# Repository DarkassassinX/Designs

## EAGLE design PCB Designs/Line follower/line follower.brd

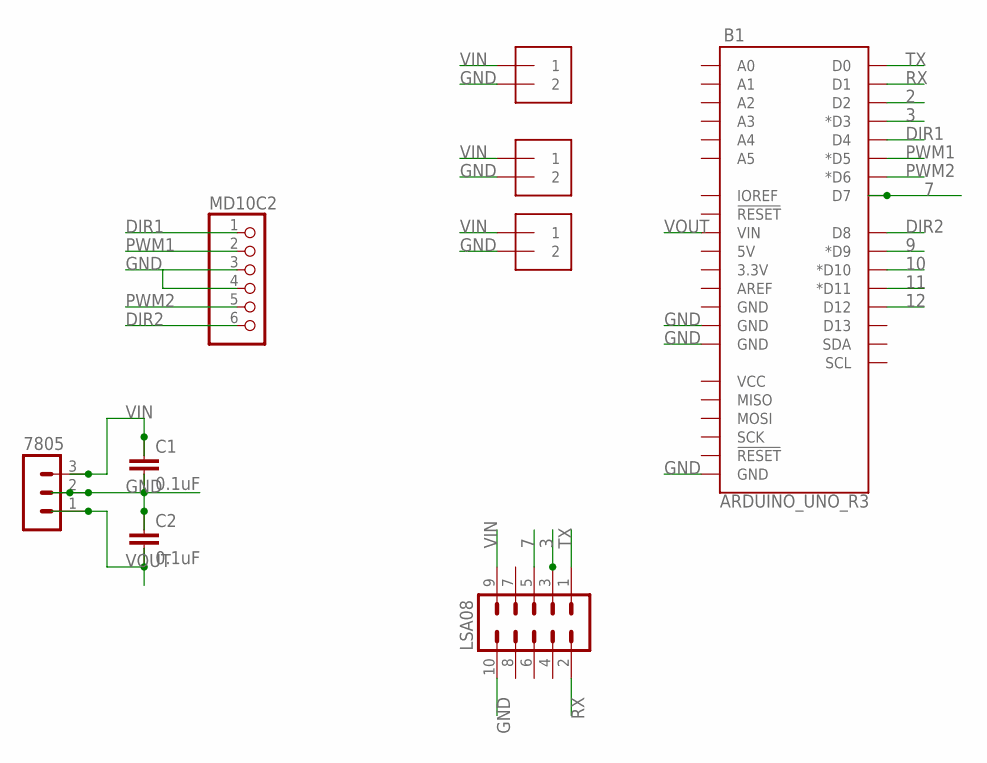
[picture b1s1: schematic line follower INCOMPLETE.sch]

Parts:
7805: MA03-1
B1: ARDUINO_UNO_R3; ARDUINO_R3
C1, C2: 0.1uF; CAP-PTH-SMALL-KIT
LSA08: MA05-2
MD1POWER, MD2POWER: 1X2-3.5MM
MD10C2: PINHD-1X6; 1X06
POWERARDUINO: 1X2-3.5MM

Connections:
2: B1.D2
3: B1.D3 (*D3), LSA08.3
7: B1.D7, LSA08.5
9: B1.D9 (*D9)
10: B1.D10 (*D10)
11: B1.D11 (*D11)
12: B1.D12
DIR1: B1.D4, MD10C2.1
DIR2: B1.D8, MD10C2.6
GND: 7805.2, B1.GND@1 (GND), B1.GND@2 (GND), B1.GND@3 (GND), C1.2, C2.1, LSA08.10, MD1POWER.2, MD2POWER.2, MD10C2.3, MD10C2.4, POWERARDUINO.2
PWM1: B1.D5 (*D5), MD10C2.2
PWM2: B1.D6 (*D6), MD10C2.5
RX: B1.D1, LSA08.2
TX: B1.D0, LSA08.1
VIN: 7805.3, C1.1, LSA08.9, MD1POWER.1, MD2POWER.1, POWERARDUINO.1
VOUT: 7805.1, B1.VIN, C2.2

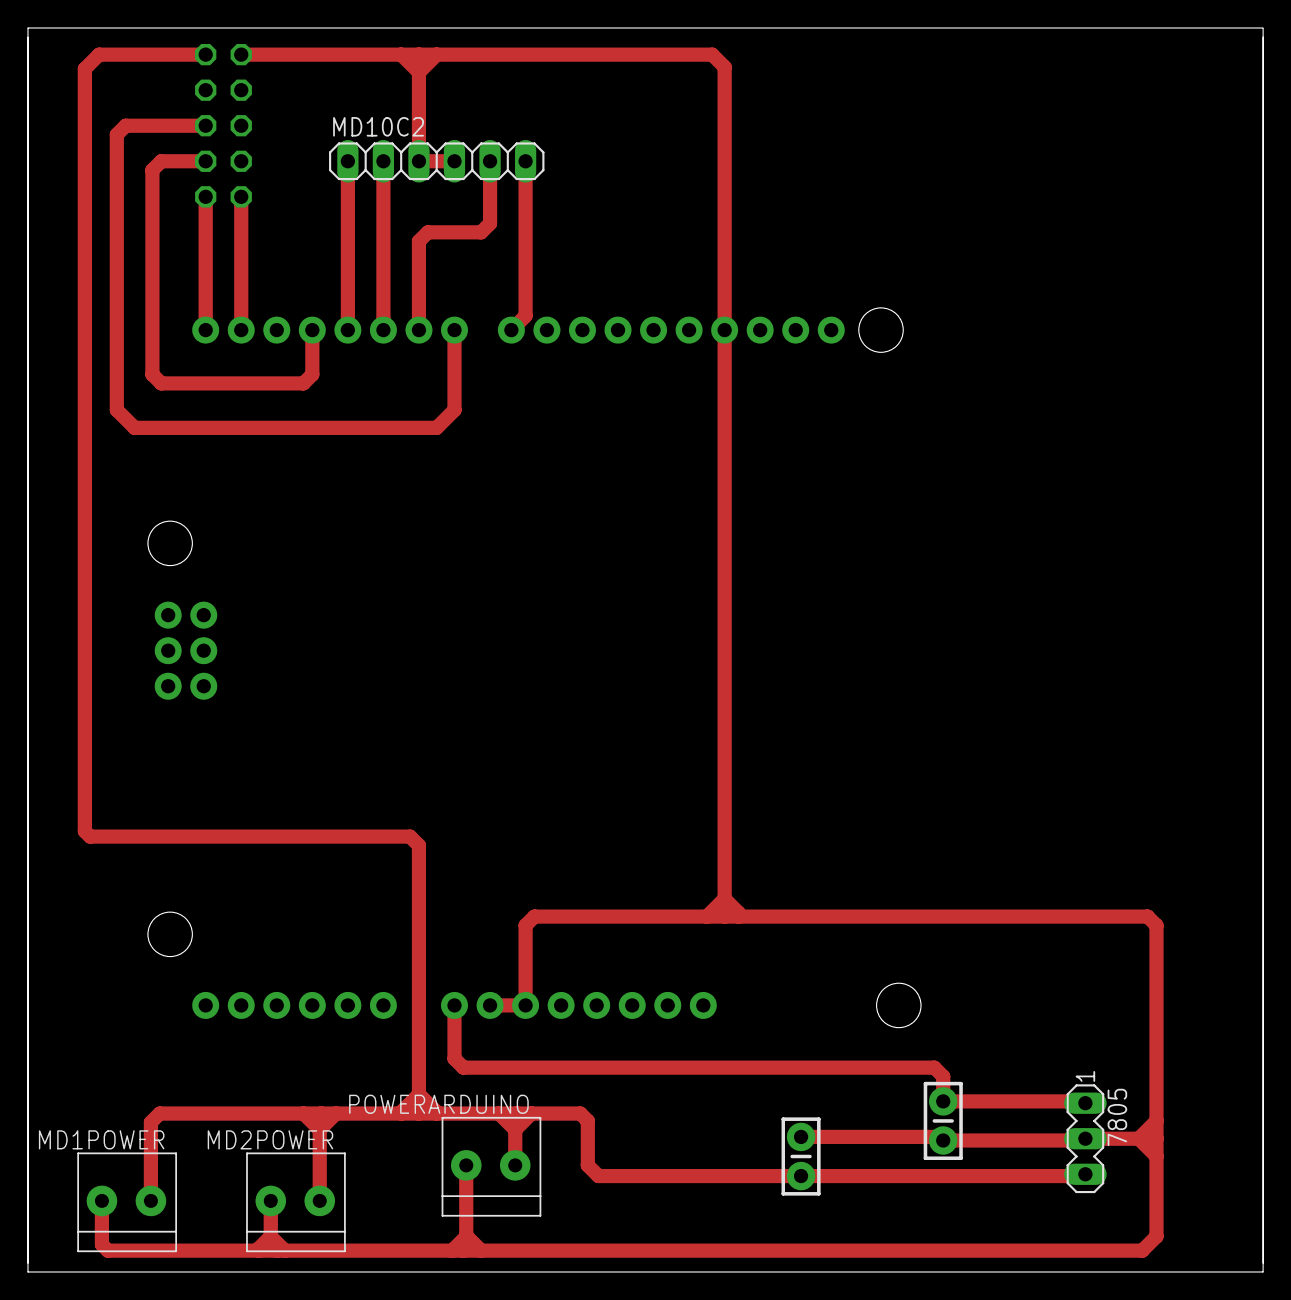
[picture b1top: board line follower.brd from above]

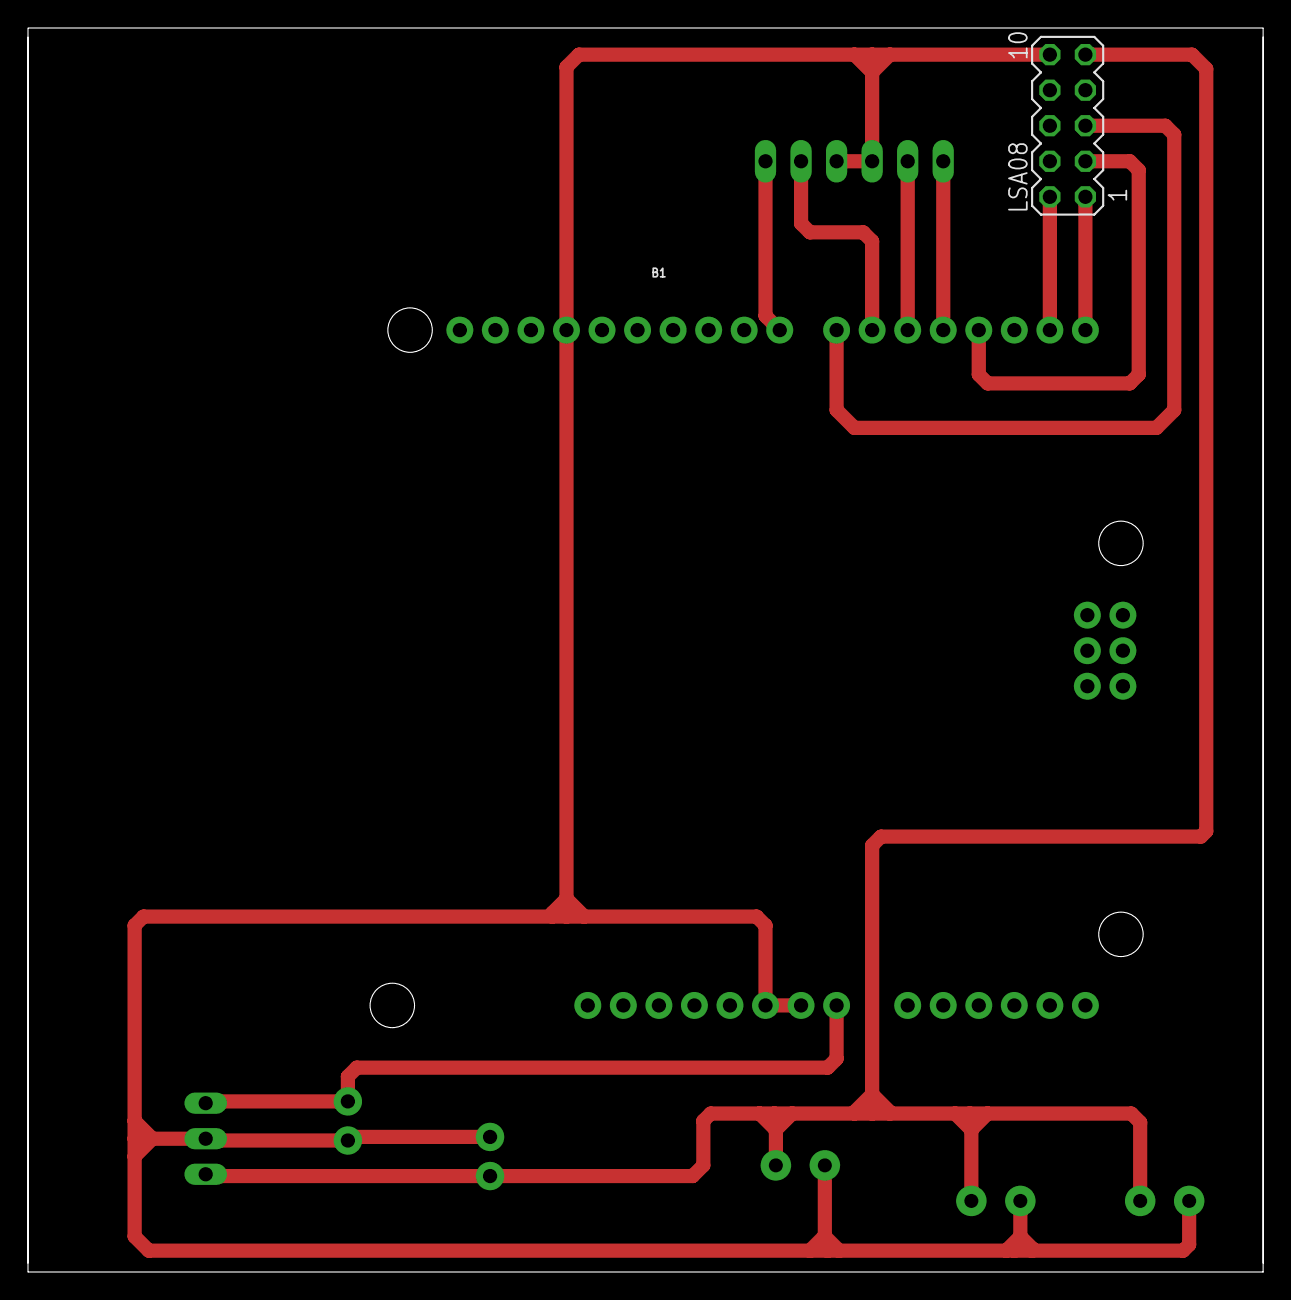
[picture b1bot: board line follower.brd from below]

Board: 2 copper layers, 88.3 x 88.9 mm, 9 parts (2 on the bottom side), 11 nets.

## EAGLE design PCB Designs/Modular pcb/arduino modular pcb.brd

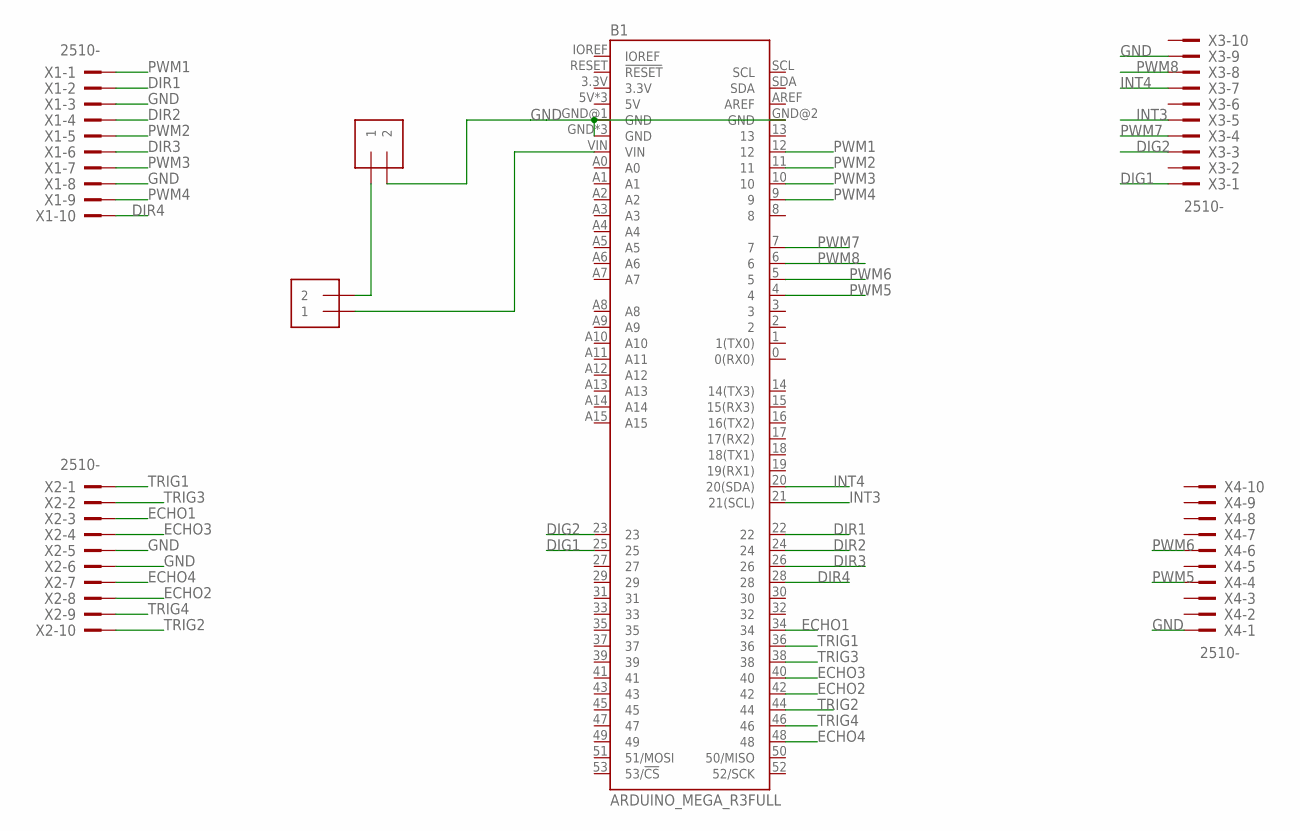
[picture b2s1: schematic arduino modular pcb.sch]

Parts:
B1: ARDUINO_MEGA_R3FULL; ARDUINO_MEGA_NO_SILK
J1, J2: 1X2-3.5MM
X1, X2, X3, X4: 2510-; PAK100/2500-10

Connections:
DIG1: B1.25, X3.1
DIG2: B1.23, X3.3
DIR1: B1.22, X1.2
DIR2: B1.24, X1.4
DIR3: B1.26, X1.6
DIR4: B1.28, X1.10
ECHO1: B1.34, X2.3
ECHO2: B1.42, X2.8
ECHO3: B1.40, X2.4
ECHO4: B1.48, X2.7
GND: B1.GND, B1.GND@1 (GND), B1.GND@2 (GND), B1.GND@3 (GND), B1.GND@4 (GND), J2.2, X1.3, X1.8, X2.5, X2.6, X3.9, X4.1
INT3: B1.21 (21(SCL)), X3.5
INT4: B1.20 (20(SDA)), X3.7
unnamed: J1.2, J2.1
unnamed: B1.VIN, J1.1
PWM1: B1.12, X1.1
PWM2: B1.11, X1.5
PWM3: B1.10, X1.7
PWM4: B1.9, X1.9
PWM5: B1.4, X4.4
PWM6: B1.5, X4.6
PWM7: B1.7, X3.4
PWM8: B1.6, X3.8
TRIG1: B1.36, X2.1
TRIG2: B1.44, X2.10
TRIG3: B1.38, X2.2
TRIG4: B1.46, X2.9

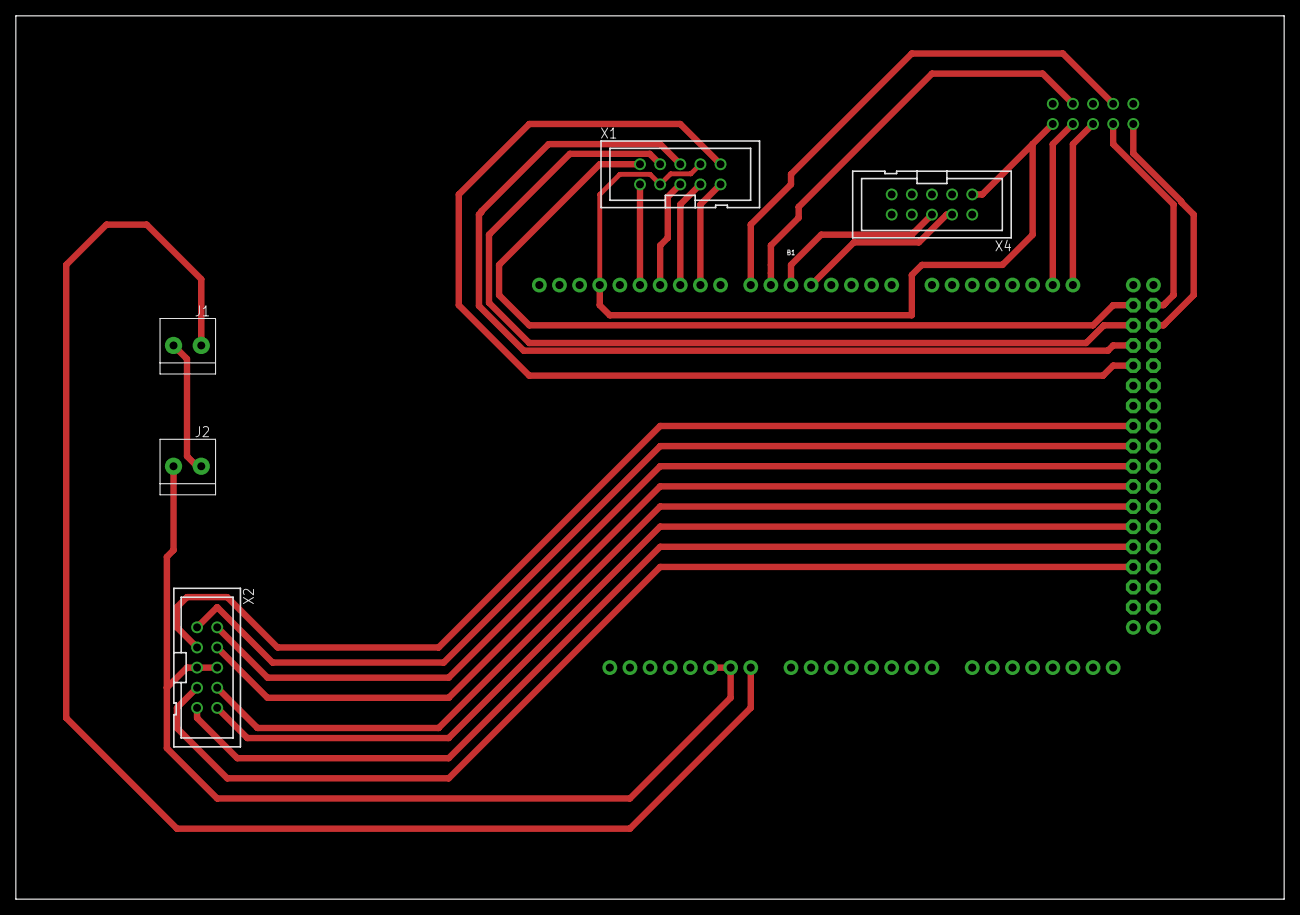
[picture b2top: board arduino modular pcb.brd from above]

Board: 2 copper layers, 160.0 x 111.4 mm, 7 parts (1 on the bottom side), 27 nets.

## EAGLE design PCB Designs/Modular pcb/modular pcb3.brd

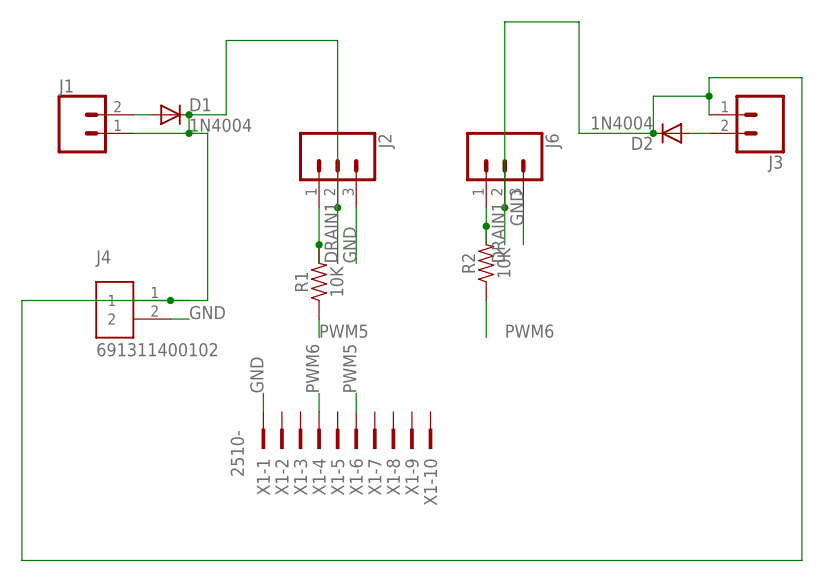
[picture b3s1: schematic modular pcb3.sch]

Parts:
D1, D2: 1N4004; DO41-10
J1, J3: CONN_02; 1X02
J2, J6: 455-1750-1-ND; 1X03
J4: 691311400102; TERMINALBLOCK_PLUGGABLE-2-7.62MM
R1, R2: 10K; 0402-TIGHT
X1: 2510-; PAK100/2500-10

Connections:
DRAIN1: D1.C, D2.C, J1.1, J2.2, J3.1, J4.1, J6.2
GND: J2.3, J4.2, J6.3, X1.1
unnamed: D1.A, J1.2
unnamed: J2.1, R1.2
unnamed: D2.A, J3.2
unnamed: J6.1, R2.2
PWM5: R1.1, X1.6
PWM6: R2.1, X1.4

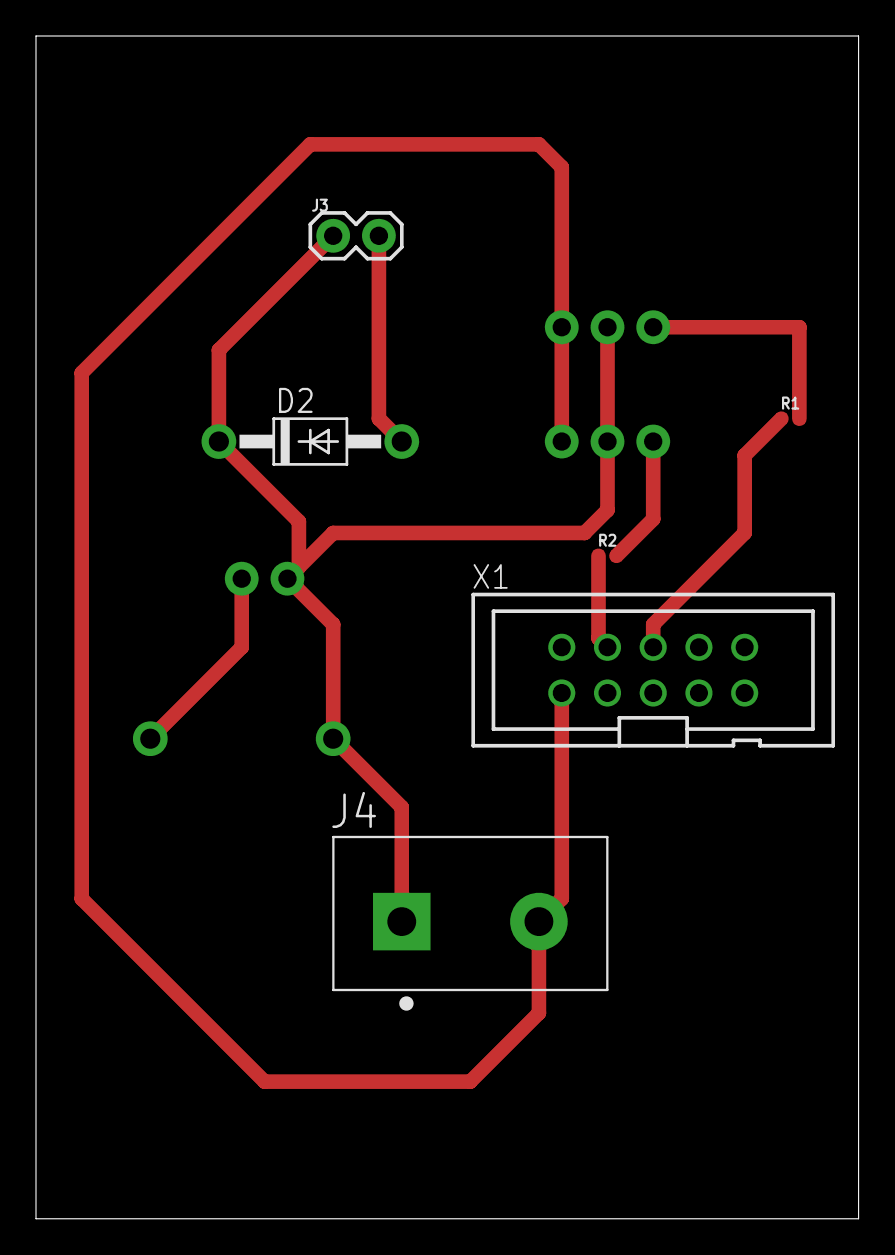
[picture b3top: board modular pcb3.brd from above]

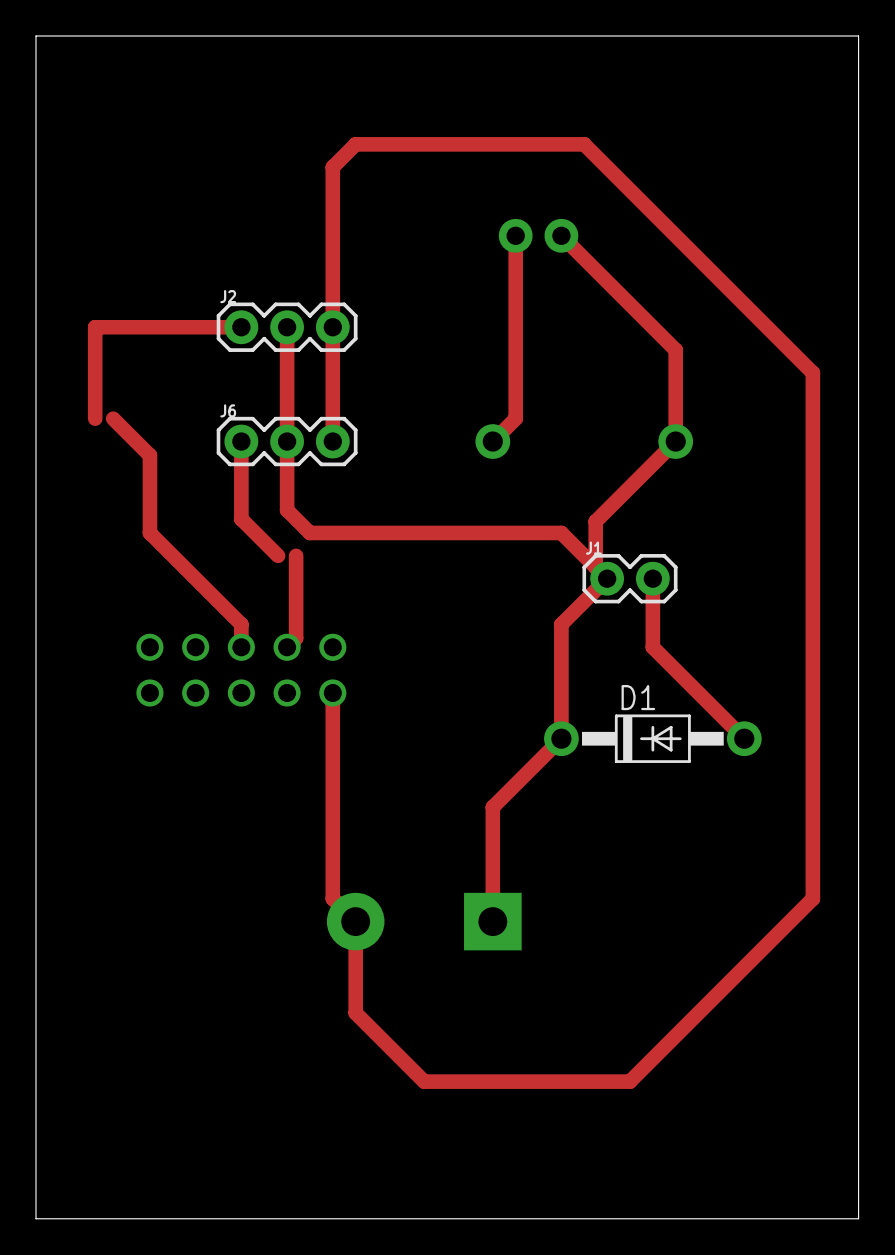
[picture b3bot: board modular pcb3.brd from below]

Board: 2 copper layers, 45.7 x 65.7 mm, 10 parts (4 on the bottom side), 8 nets.

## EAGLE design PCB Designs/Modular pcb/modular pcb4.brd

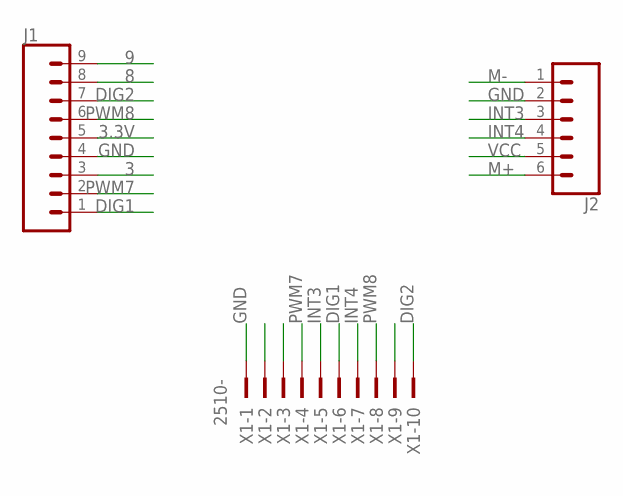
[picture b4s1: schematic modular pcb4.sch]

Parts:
J1: CONN_09; 1X09
J2: CONN_06FEMALE_LOCK; 1X06_FEMALE_LOCK.010
X1: 2510-; PAK100/2500-10

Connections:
3: J1.3
3.3: X1.2
3.3V: J1.5
8: J1.8
9: J1.9
DIG1: J1.1, X1.6
DIG2: J1.7, X1.10
E: X1.3
GND: J1.4, J2.2, X1.1
INT3: J2.3, X1.5
INT4: J2.4, X1.7
M+: J2.6
M-: J2.1
PWM7: J1.2, X1.4
PWM8: J1.6, X1.8
VCC: J2.5, X1.9

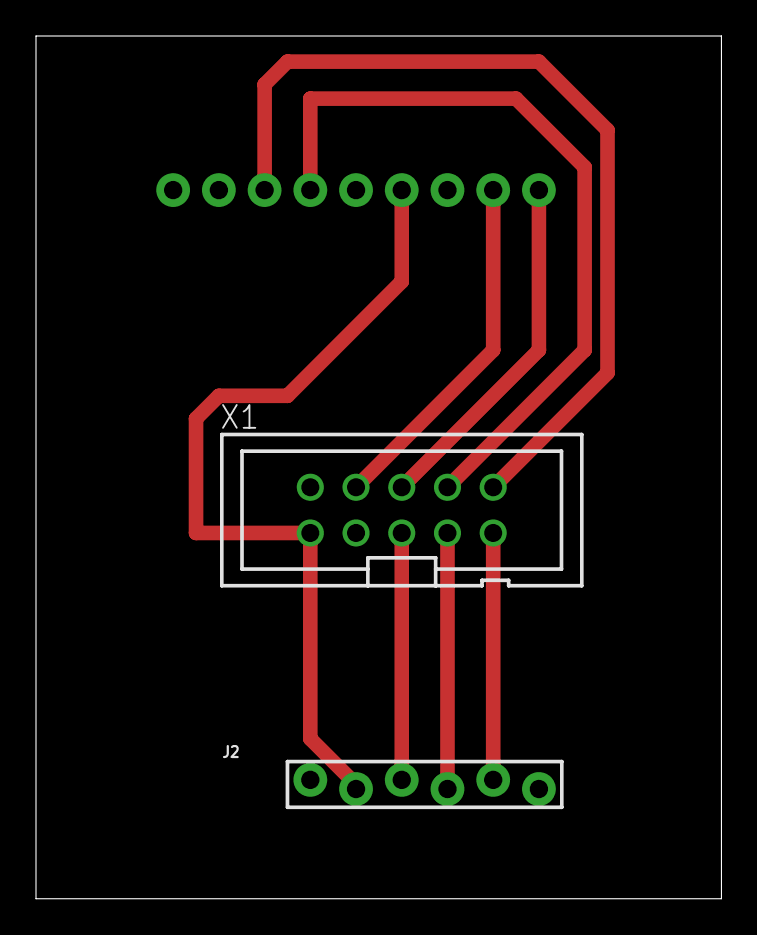
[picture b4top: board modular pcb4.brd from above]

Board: 2 copper layers, 38.1 x 47.9 mm, 3 parts (1 on the bottom side), 8 nets.

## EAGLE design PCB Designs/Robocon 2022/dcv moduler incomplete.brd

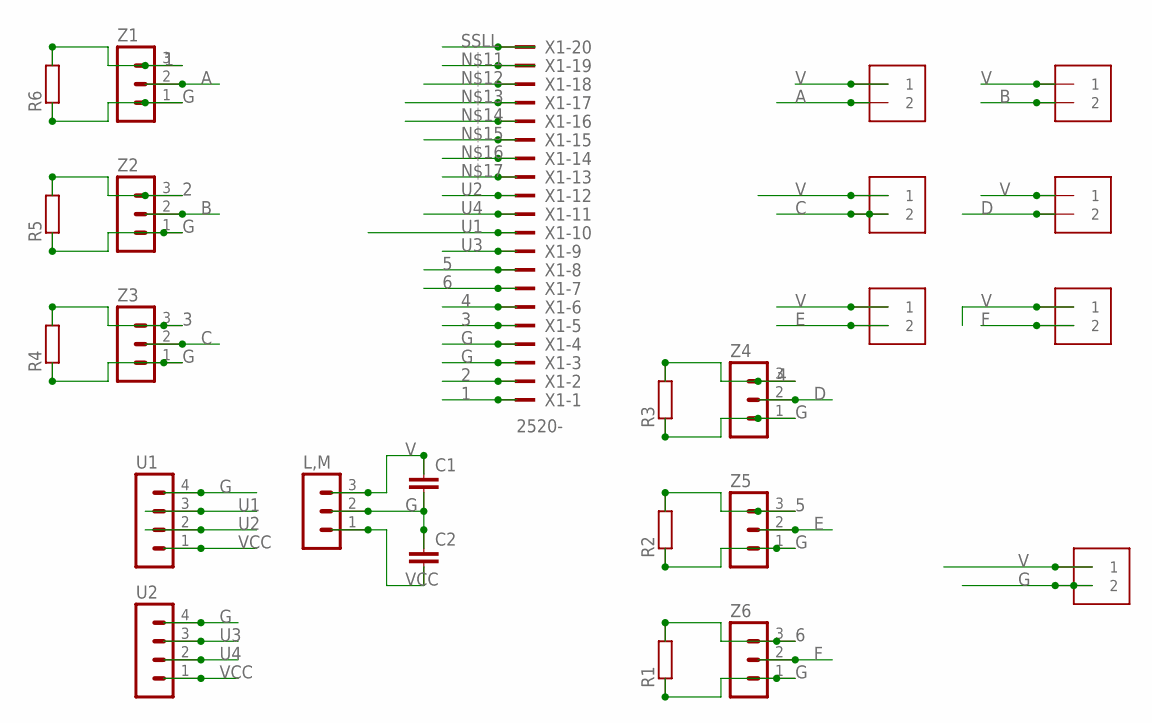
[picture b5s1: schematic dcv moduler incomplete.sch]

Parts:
C1, C2: C2,5-3; C2.5-3
J1, J2, J3, J4, J5, J6, J7: 1X2-3.5MM
L,M: MA03-1
R1, R2, R3, R4, R5, R6: R-EU_0204_5; 0204/5
U1, U2: MA04-1
X1: 2520-; PAK100/2500-20
Z1, Z2, Z3, Z4, Z5, Z6: MA03-1

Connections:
1: R6.2, X1.1, Z1.3
2: R5.2, X1.2, Z2.3
3: R4.2, X1.5, Z3.3
4: R3.2, X1.6, Z4.3
5: R2.2, X1.8, Z5.3
6: R1.2, X1.7, Z6.3
A: J1.2, Z1.2
B: J2.2, Z2.2
C: J3.2, Z3.2
D: J4.2, Z4.2
E: J5.2, Z5.2
F: J6.2, Z6.2
G: C1.2, C2.1, J7.2, L,M.2, R1.1, R2.1, R3.1, R4.1, R5.1, R6.1, U1.4, U2.4, X1.3, X1.4, Z1.1, Z2.1, Z3.1, Z4.1, Z5.1, Z6.1
SSLL: X1.20
U1: U1.3, X1.10
U2: U1.2, X1.12
U3: U2.3, X1.9
U4: U2.2, X1.11
V: C1.1, J1.1, J2.1, J3.1, J4.1, J5.1, J6.1, J7.1, L,M.3
VCC: C2.2, L,M.1, U1.1, U2.1

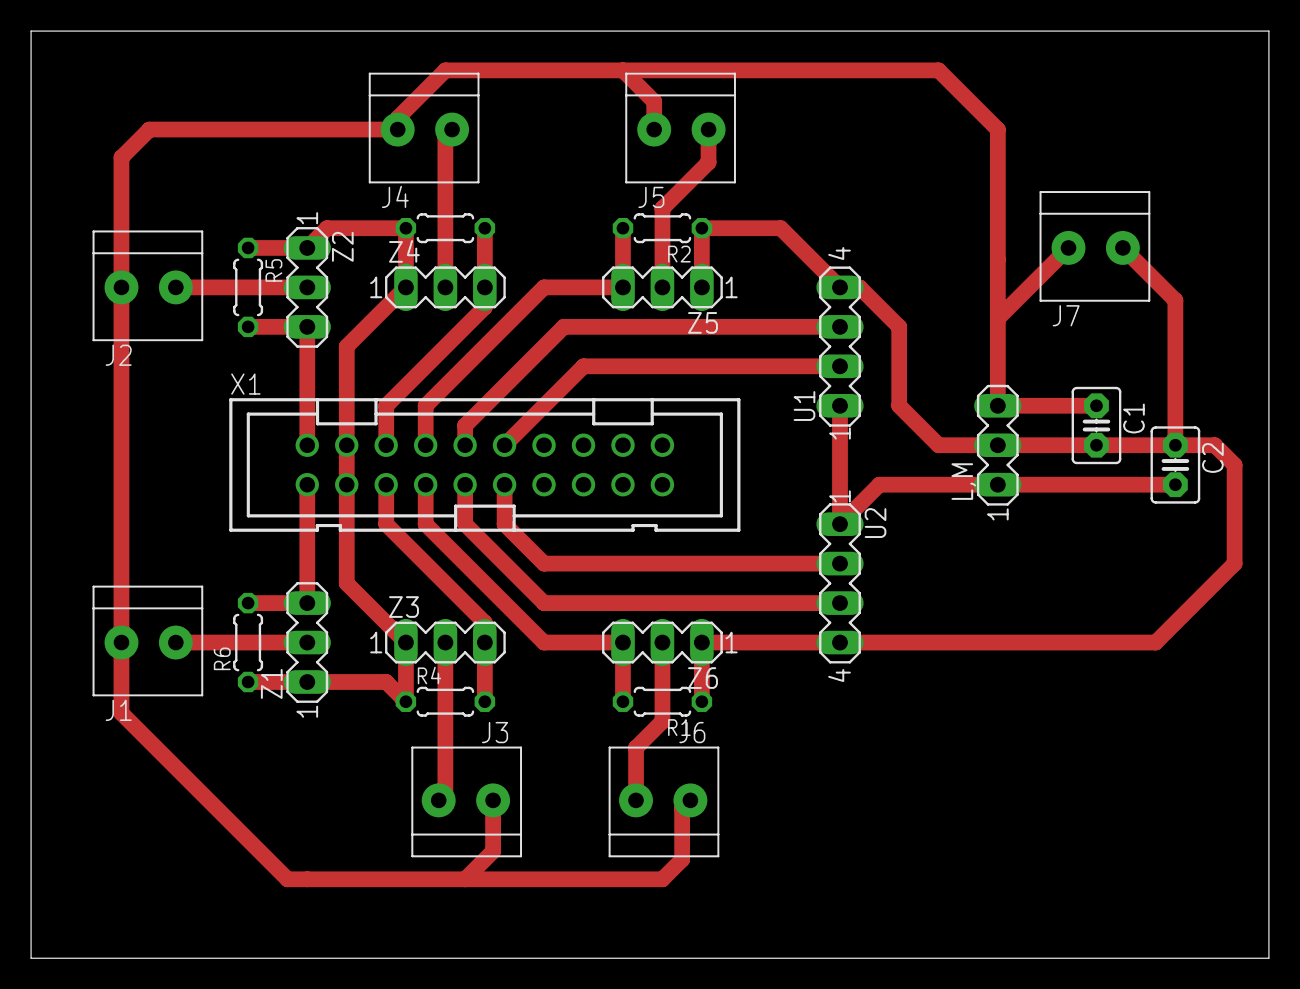
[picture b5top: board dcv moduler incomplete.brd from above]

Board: 2 copper layers, 79.7 x 59.7 mm, 25 parts (0 on the bottom side), 19 nets.

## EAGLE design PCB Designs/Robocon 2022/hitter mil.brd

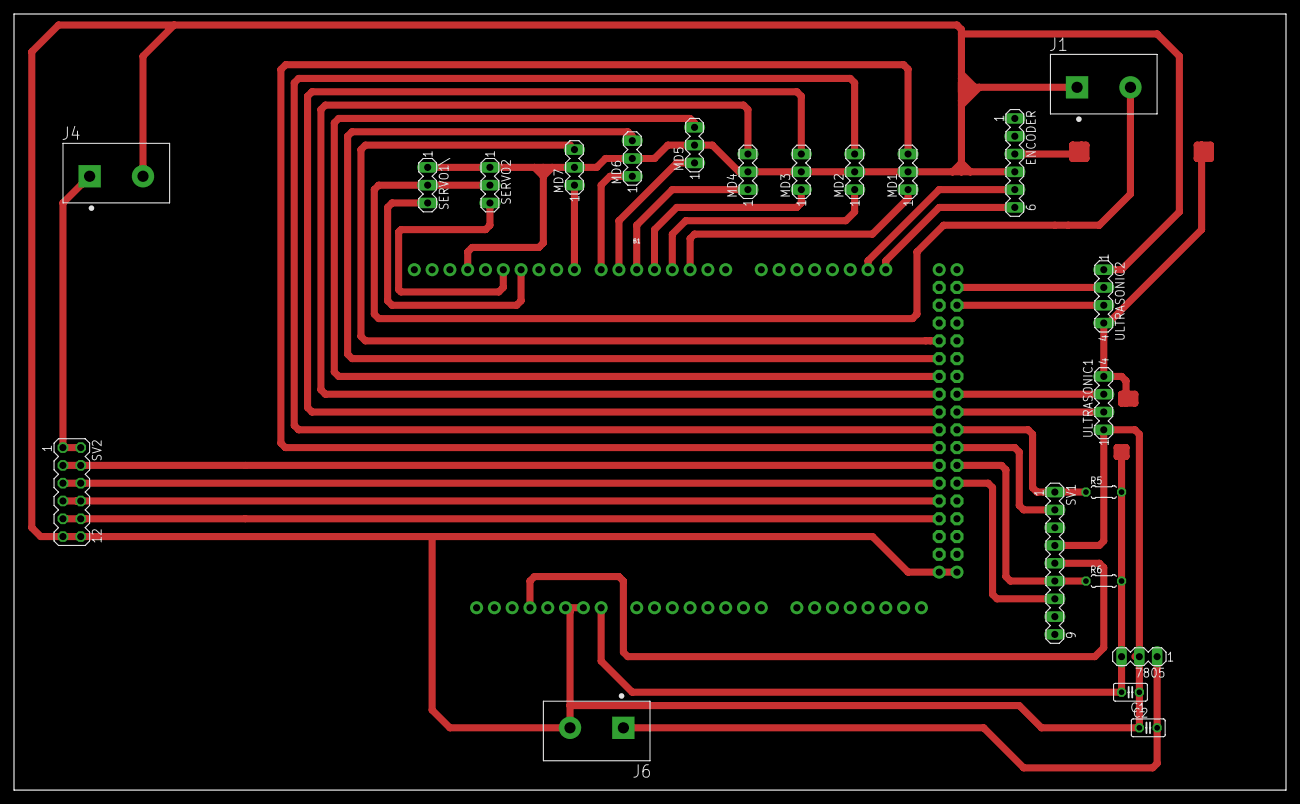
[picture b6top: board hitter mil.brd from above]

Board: 2 copper layers, 181.6 x 110.8 mm, 23 parts (0 on the bottom side), 36 nets.

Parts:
7805: MA03-1
B1: ARDUINO_MEGA_R3FULL; ARDUINO_MEGA_NO_SILK
C1, C2: C025-025X050
ENCODER: MA06-1
J1, J4, J6: 691311400102; TERMINALBLOCK_PLUGGABLE-2-7.62MM
MD1, MD2, MD3, MD4, MD5, MD6, MD7: MA03-1
R5, R6: 0204/5
SERVO1\, SERVO2: MA03-1
SV1: MA09-1
SV2: MA06-2
ULTRASONIC1, ULTRASONIC2: MA04-1

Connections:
2: B1.2, MD1.1
3: B1.3, MD2.1
3.3: B1.3.3V, SV1.5
4: B1.4, MD3.1
5: B1.5, MD4.1
6: B1.6, MD5.1
7: B1.7, MD6.1
8: B1.8, MD7.1
11: B1.11, SERVO1\.3
12: B1.12, SERVO2.3
20: B1.20, ENCODER.5
21: B1.21, ENCODER.6
23: B1.23, ULTRASONIC2.2
25: B1.25, ULTRASONIC2.3
28: B1.28, MD7.3
30: B1.30, MD6.3
32: B1.32, MD5.3
34: B1.34, MD4.3
35: B1.35, ULTRASONIC1.3
36: B1.36, MD3.3
37: B1.37, ULTRASONIC1.2
38: B1.38, MD2.3
39: B1.39, R5.1, SV1.1
40: B1.40, MD1.3
41: B1.41, SV1.2
42: B1.42, SV2.3, SV2.4
43: B1.43, R6.1, SV1.6
44: B1.44, SV2.5, SV2.6
45: B1.45, SV1.7
46: B1.46, SV2.7, SV2.8
48: B1.48, SV2.9, SV2.10
GND: 7805.2, B1.GND, B1.GND@1, B1.GND@2, B1.GND@3, B1.GND@4, C1.1, C2.1, ENCODER.4, J1.1, J4.2, J6.2, MD1.2, MD2.2, MD3.2, MD4.2, MD5.2, MD6.2, MD7.2, SERVO1\.1, SERVO2.1, SV1.4, SV2.11, SV2.12, ULTRASONIC1.1, ULTRASONIC2.1
LOAD: J4.1, SV2.1, SV2.2
VC: J1.2, SERVO1\.2, SERVO2.2
VCC: 7805.1, C2.2, J6.1
VOUT: 7805.3, B1.VIN, C1.2, ENCODER.3, R5.2, R6.2, ULTRASONIC1.4, ULTRASONIC2.4

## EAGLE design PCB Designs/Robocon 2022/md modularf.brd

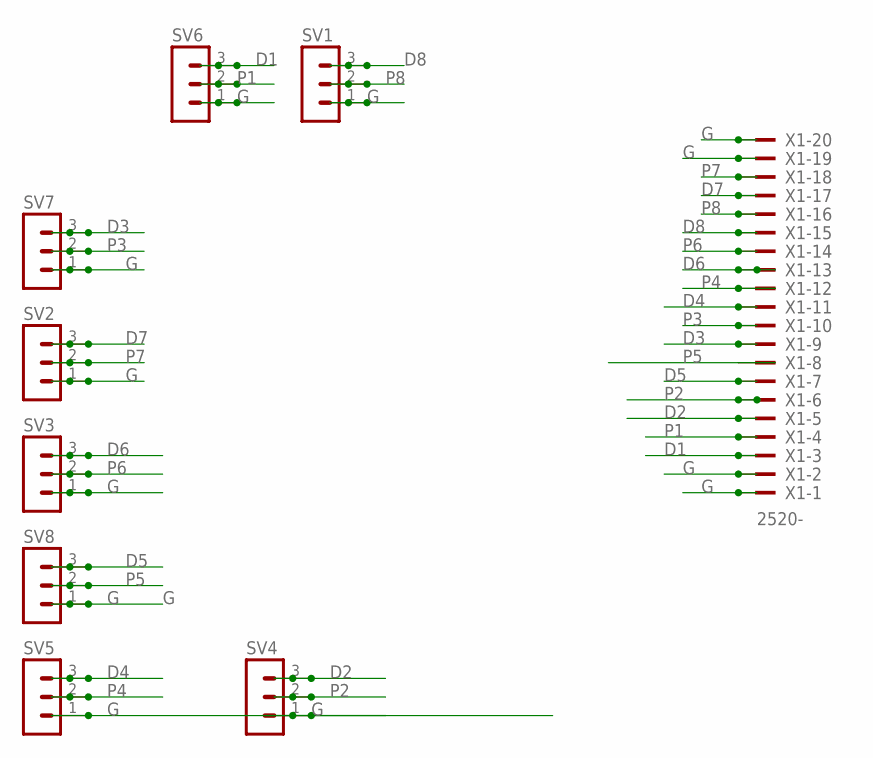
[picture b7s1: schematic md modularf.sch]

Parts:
SV1, SV2, SV3, SV4, SV5, SV6, SV7, SV8: MA03-1
X1: 2520-; PAK100/2500-20

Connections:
D1: SV6.3, X1.3
D2: SV4.3, X1.5
D3: SV7.3, X1.9
D4: SV5.3, X1.11
D5: SV8.3, X1.7
D6: SV3.3, X1.13
D7: SV2.3, X1.17
D8: SV1.3, X1.15
G: SV1.1, SV2.1, SV3.1, SV4.1, SV5.1, SV6.1, SV7.1, SV8.1, X1.1, X1.2, X1.19, X1.20
P1: SV6.2, X1.4
P2: SV4.2, X1.6
P3: SV7.2, X1.10
P4: SV5.2, X1.12
P5: SV8.2, X1.8
P6: SV3.2, X1.14
P7: SV2.2, X1.18
P8: SV1.2, X1.16

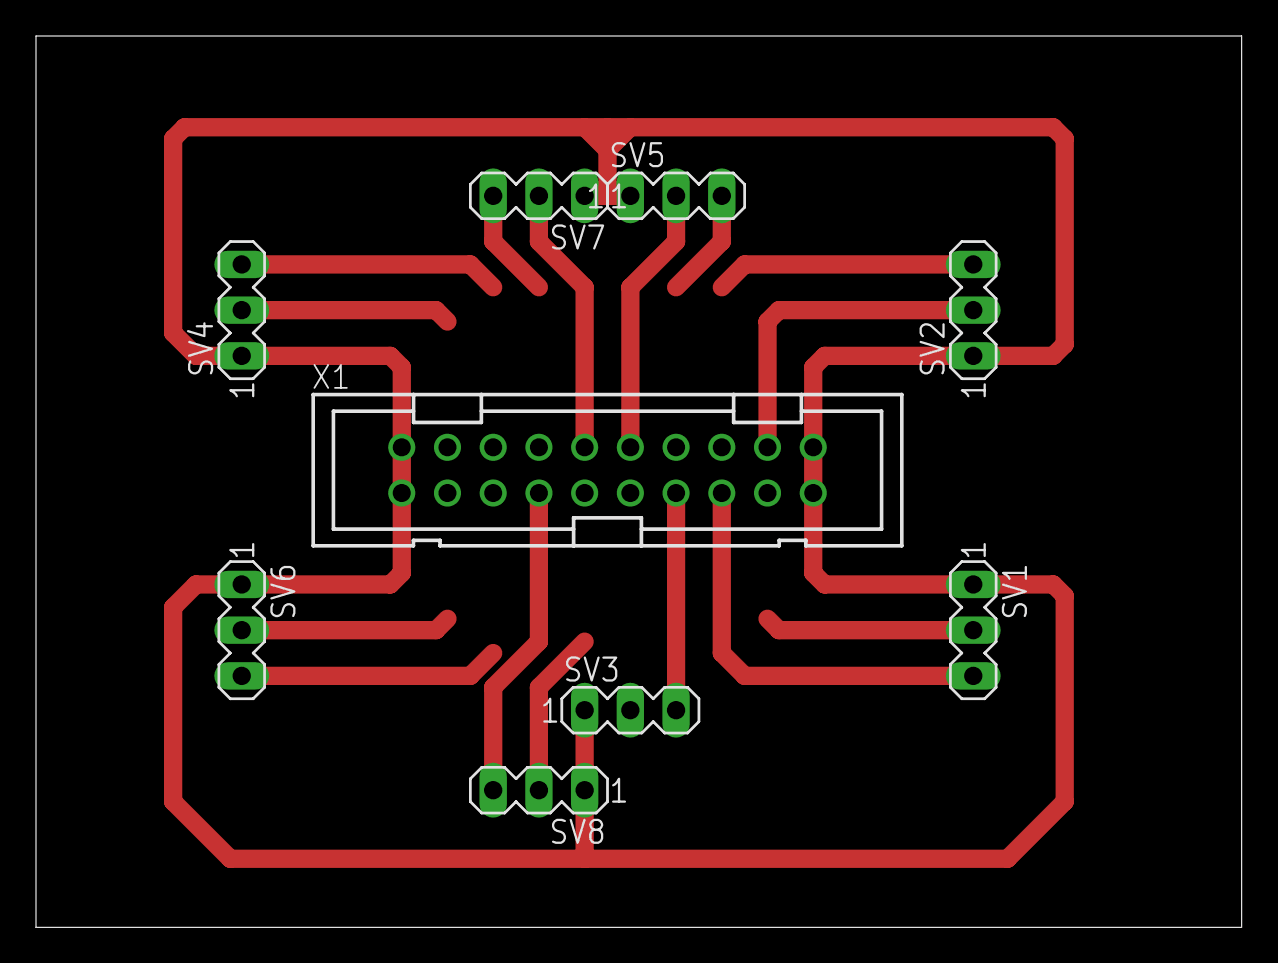
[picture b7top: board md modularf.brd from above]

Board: 2 copper layers, 67.0 x 49.5 mm, 9 parts (0 on the bottom side), 17 nets.

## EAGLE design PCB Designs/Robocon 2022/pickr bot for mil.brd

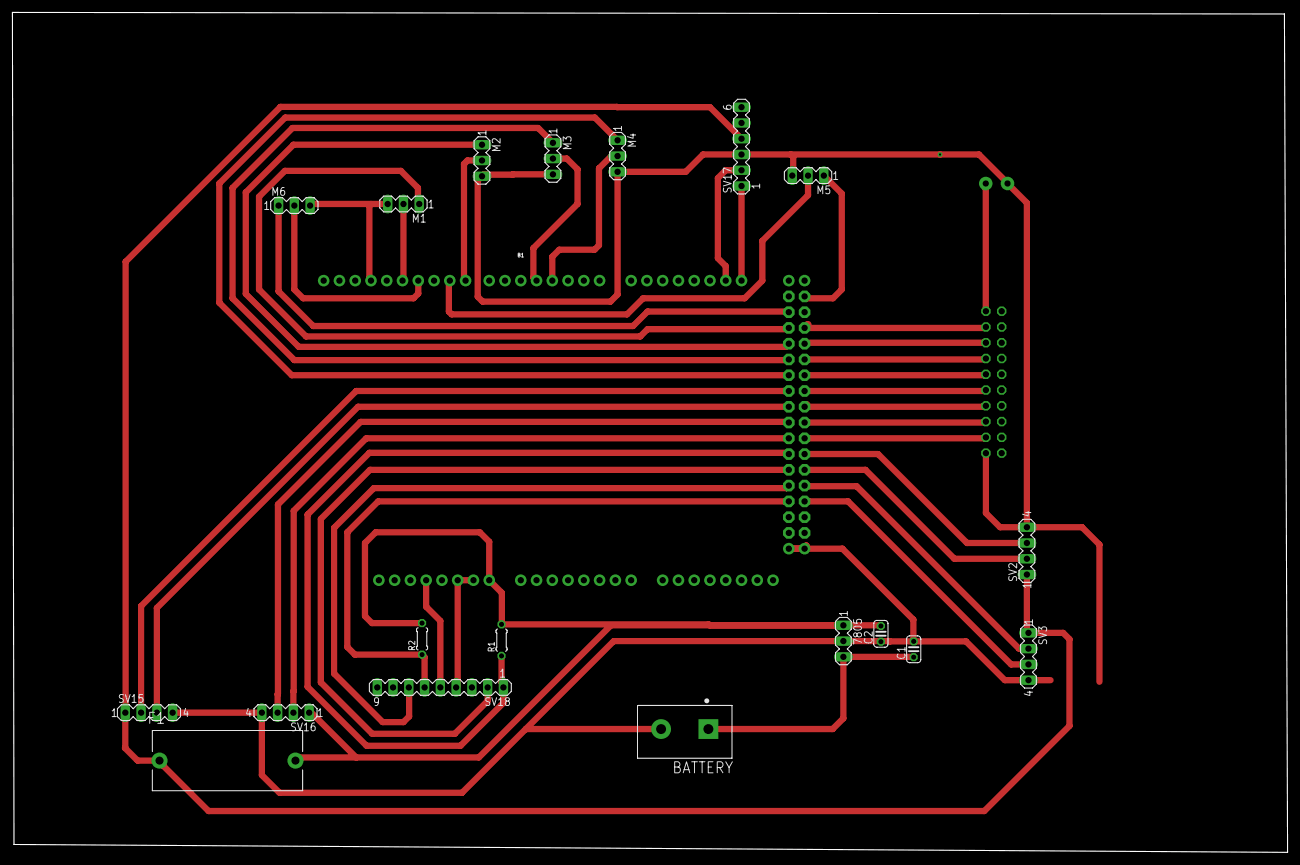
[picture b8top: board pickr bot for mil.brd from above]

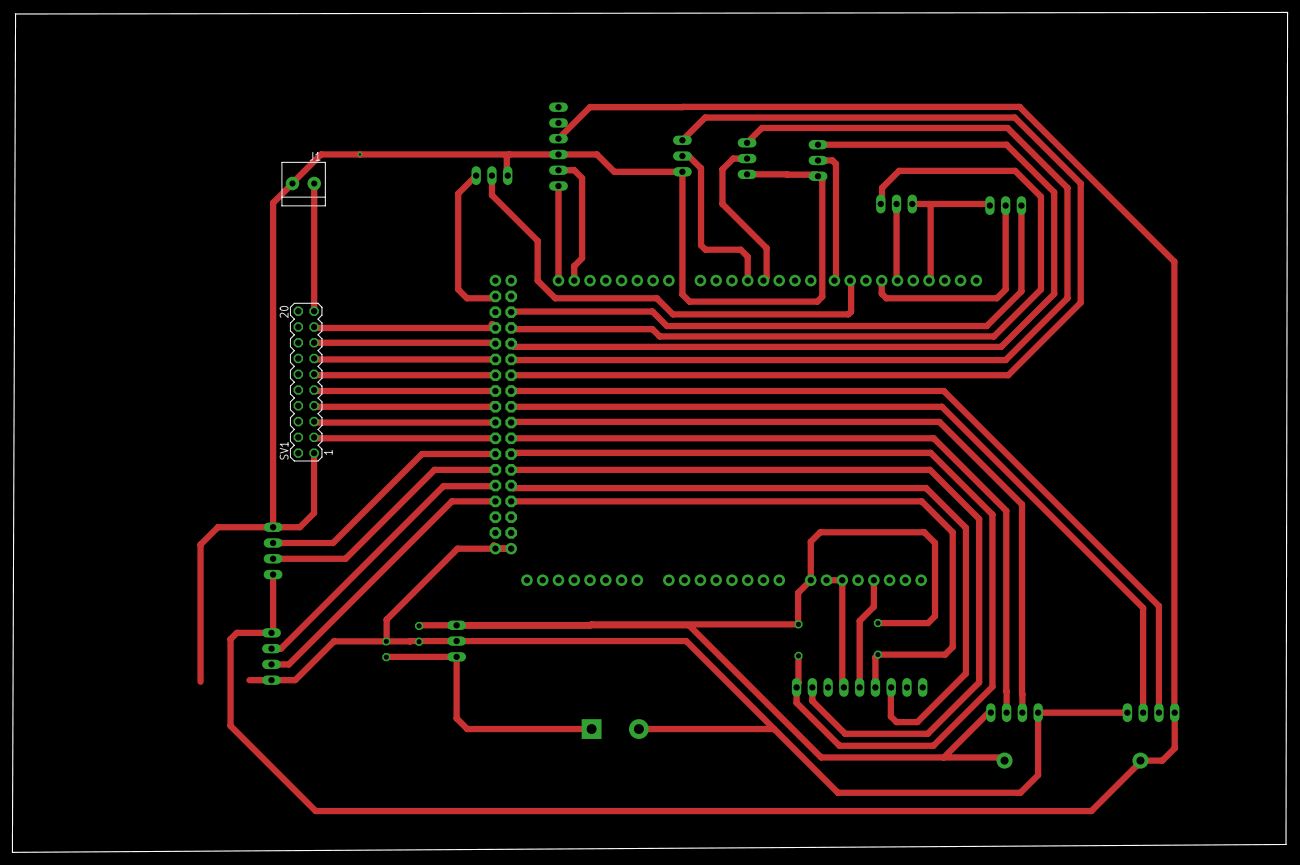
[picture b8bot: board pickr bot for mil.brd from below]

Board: 2 copper layers, 205.4 x 135.3 mm, 22 parts (2 on the bottom side), 39 nets.

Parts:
7805: MA03-1
B1: ARDUINO_MEGA_R3FULL; ARDUINO_MEGA_NO_SILK
BATTERY: 691311400102; TERMINALBLOCK_PLUGGABLE-2-7.62MM
C1, C2: C025-024X044
F1: 4527
J1: 1X2-3.5MM
M1, M2, M3, M4, M5, M6: MA03-1
R1, R2: 0204/5
SV1: MA10-2
SV2, SV3, SV15, SV16: MA04-1
SV17: MA06-1
SV18: MA09-1

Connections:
3.3: B1.3.3V, SV18.5
43: B1.43, SV2.3
45: B1.45, SV2.2
47: B1.47, SV3.2
49: B1.49, SV3.3
A: B1.48, R2.1, SV18.6
C: B1.44, SV18.2
CL: B1.46, SV18.7
D: B1.42, R1.1, SV18.1
D1: B1.26, M1.1
D2: B1.28, M2.1
D3: B1.30, M3.1
D4: B1.32, M4.1
D5: B1.23, M5.1
D6: B1.24, M6.1
E1: B1.36, SV15.3
E2: B1.38, SV16.3
G: 7805.2, B1.GND, B1.GND@1, B1.GND@2, B1.GND@3, B1.GND@4, BATTERY.2, C1.2, C2.1, J1.2, M1.3, M2.3, M3.3, M4.3, M5.3, M6.3, SV1.1, SV2.4, SV3.4, SV15.4, SV16.4, SV17.3, SV18.4
G2: B1.27, SV1.17
G3: B1.29, SV1.15
G4: B1.31, SV1.13
G5: B1.33, SV1.11
G6: B1.35, SV1.9
G7: B1.37, SV1.7
G8: B1.39, SV1.5
H1: B1.20, SV17.2
H2: B1.21, SV17.1
unnamed: B1.41, SV1.3
P1: B1.12, M1.2
P2: B1.8, M2.2
P3: B1.4, M3.2
P4: B1.3, M4.2
P5: B1.9, M5.2
P6: B1.11, M6.2
PO: J1.1, SV1.19
T1: B1.34, SV15.2
T2: B1.40, SV16.2
V: 7805.1, B1.VIN, C2.2, F1.1, F1.2, R1.2, R2.2, SV2.1, SV3.1, SV15.1, SV16.1, SV17.4
VB: 7805.3, BATTERY.1, C1.1

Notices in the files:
parts and their libraries:
SparkFun-Boards: Licensing: Creative Commons ShareAlike 4.0 International - https://creativecommons.org/licenses/by-sa/4.0
